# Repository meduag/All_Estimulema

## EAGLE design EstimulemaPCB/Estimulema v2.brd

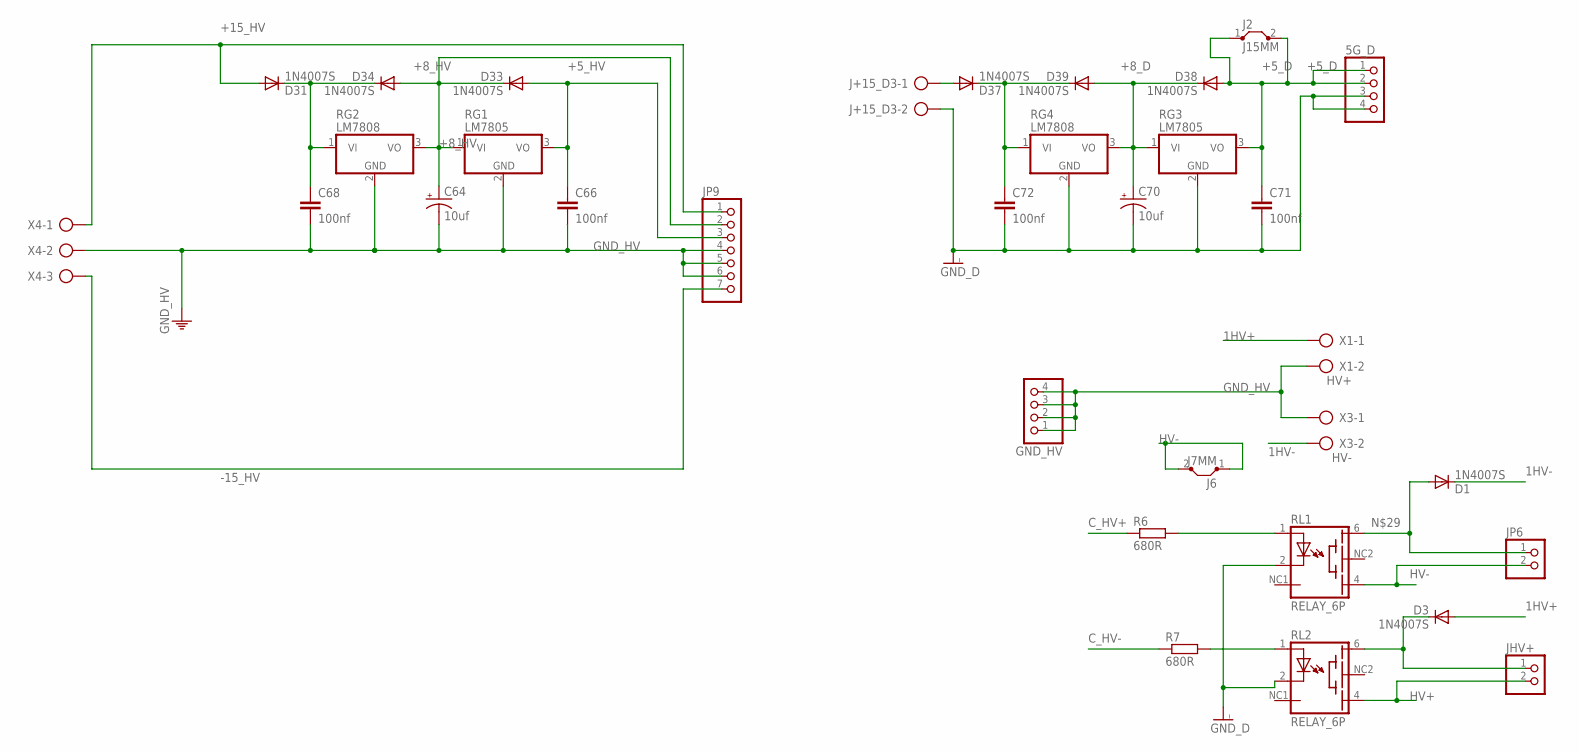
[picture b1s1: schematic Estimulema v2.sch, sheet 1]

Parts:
5G_D: PINHD-1X4; 1X04
C64, C70: 10uf; E2-5
C66, C68, C71, C72: 100nf; C025-024X044
D1, D3, D31, D33, D34, D37, D38, D39: 1N4007S; DIODO4MM
GND_HV: PINHD-1X4; 1X04
J2: J15MM; 15
J6: J7MM; 07
J+15_D3: AK300/2
JHV+: PINHD-1X2; 1X02
JP6: PINHD-1X2; 1X02
JP9: PINHD-1X7; 1X07
R6, R7: 680R; RESISTENCIA_0805
RG1, RG3: LM7805; TO220V
RG2, RG4: LM7808; TO220V
RL1, RL2: RELAY_6P; TS210
X1: HV+; AK300/2
X3: HV-; AK300/2
X4: AK300/3

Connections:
1HV+: D3.A, X1.1
1HV-: D1.C, X3.2
+5_D: 5G_D.1, 5G_D.2, C71.1, D38.A, J2.1, J2.2, RG3.3 (VO); also elsewhere on the board
+5_HV: C66.1, D33.A, JP9.3, RG1.3 (VO); also elsewhere on the board
+8_D: C70.+, D38.C, D39.A, RG3.1 (VI), RG4.3 (VO)
+8_HV: C64.+, D33.C, D34.A, JP9.2, RG1.1 (VI), RG2.3 (VO)
+15_HV: D31.A, JP9.1, X4.1; also elsewhere on the board
-15_HV: JP9.7, X4.3; also elsewhere on the board
C_HV+: R6.1; also elsewhere on the board
C_HV-: R7.1; also elsewhere on the board
GND_D: 5G_D.3, 5G_D.4, C70.-, C71.2, C72.2, J+15_D3.2, RG3.2 (GND), RG4.2 (GND), RL1.2 (C), RL2.2 (C); also elsewhere on the board
GND_HV: C64.-, C66.2, C68.2, GND_HV.1, GND_HV.2, GND_HV.3, GND_HV.4, JP9.4, JP9.5, JP9.6, RG1.2 (GND), RG2.2 (GND), X1.2, X3.1, X4.2; also elsewhere on the board
HV+: JHV+.2, RL2.4 (EMI); also elsewhere on the board
HV-: J6.1, J6.2, JP6.2, RL1.4 (EMI); also elsewhere on the board
unnamed: D37.A, J+15_D3.1
unnamed: R6.2, RL1.1 (A)
unnamed: R7.2, RL2.1 (A)
unnamed: D1.A, JP6.1, RL1.6 (BAS)
unnamed: D3.C, JHV+.1, RL2.6 (BAS)
unnamed: C68.1, D31.C, D34.C, RG2.1 (VI)
unnamed: C72.1, D37.C, D39.C, RG4.1 (VI)

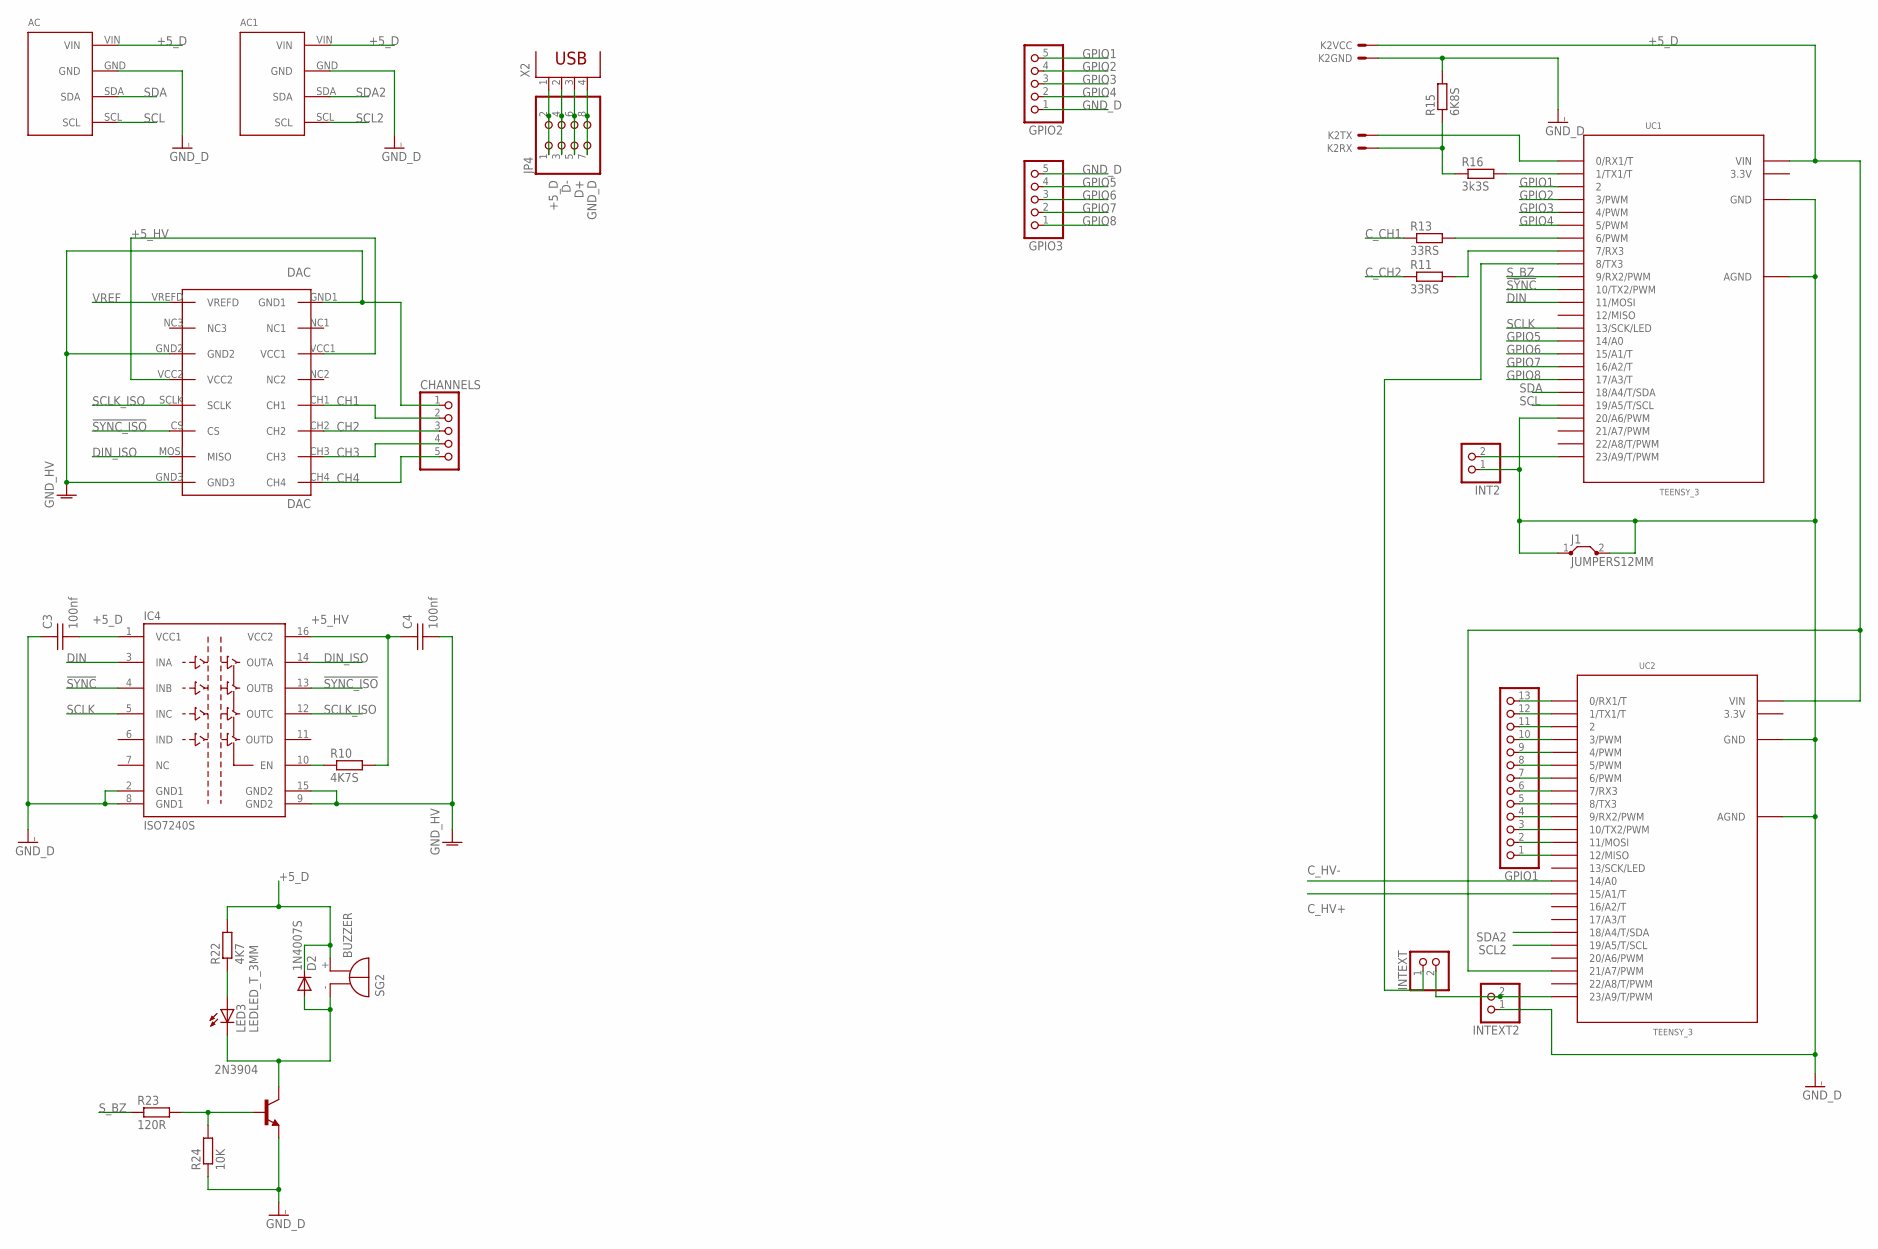
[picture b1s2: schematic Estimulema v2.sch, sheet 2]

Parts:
2N3904: 29-NPN-TO92-EBC; TO92-EBC
AC: CONECTOR_ACELEROMETRO_MPU6050CONECTOR_MPU6050; MPU6050
AC1: MPU6050
C3, C4: 100nf; CAP_CER_SMD-0805
CHANNELS: PINHD-1X5; 1X05
D2: 1N4007S; DIODO4MM
DAC: DAC; DACMOD_P
GPIO1: PINHD-1X13; 1X13
GPIO2, GPIO3: PINHD-1X5; 1X05
IC4: ISO7240S; SO-16DW
INT2: PINHD-1X2; 1X02
INTEXT, INTEXT2: PINHD-1X2; 1X02
J1: JUMPERS12MM; 12
JP4: PINHD-2X4; 2X04
K2: HC-06; CONECTOR_BTHC-06
LED3: LEDLED_T_3MM; LED3MM
R10: 4K7S; RESISTENCIA_0805
R11, R13: 33RS; RESISTENCIA_0805
R15: 6K8S; RESISTENCIA_0805
R16: 3k3S; RESISTENCIA_0805
R22: 4K7; RESISTENCIA_0805
R23: 120R; RESISTENCIA_0805
R24: 10K; RESISTENCIA_0805
SG2: BUZZER
UC1, UC2: TEENSY_3; TEENSY_3.0-3.2_DIL
X2: PN61729

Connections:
3.3V: UC1.3.3V, UC2.3.3V
!SYNC: IC4.4 (INB), UC1.10 (10/TX2/PWM)
!SYNC_ISO: DAC.CS, IC4.13 (OUTB)
+5_D: AC.VIN, AC1.VIN, C3.2, D2.C, IC4.1 (VCC1), JP4.1, JP4.2, K2.1, R22.2, SG2.+ (-), UC1.VIN, UC2.21/A7 (21/A7/PWM), UC2.VIN, X2.1; also elsewhere on the board
+5_HV: C4.1, DAC.VCC1, DAC.VCC2, IC4.16 (VCC2), R10.2; also elsewhere on the board
CH1: CHANNELS.2, DAC.CH1; also elsewhere on the board
CH2: CHANNELS.3, DAC.CH2; also elsewhere on the board
CH3: CHANNELS.4, DAC.CH3
CH4: CHANNELS.5, DAC.CH4
C_15D: GPIO1.11, UC2.2
C_CH1: R13.1; also elsewhere on the board
C_CH2: R11.1; also elsewhere on the board
C_HV+: UC2.15/A1 (15/A1/T); also elsewhere on the board
C_HV-: UC2.14/A0; also elsewhere on the board
D+: JP4.5, JP4.6, X2.3
D-: JP4.3, JP4.4, X2.2
DIN: IC4.3 (INA), UC1.11 (11/MOSI)
DIN_ISO: DAC.MOSI (MISO), IC4.14 (OUTA)
GNDI: C3.1, IC4.2 (GND1), IC4.8 (GND1)
GND_D: 2N3904.E, AC.GND, AC1.GND, GPIO2.1, GPIO3.5, INT2.1, INTEXT2.1, J1.1, J1.2, JP4.7, JP4.8, K2.2, R15.2, R24.1, UC1.20/A6 (20/A6/PWM), UC1.AGND, UC1.GND, UC2.AGND, UC2.GND, X2.4; also elsewhere on the board
GND_HV: C4.2, CHANNELS.1, DAC.GND1, DAC.GND2, DAC.GND3, IC4.9 (GND2), IC4.15 (GND2); also elsewhere on the board
GPIO1: GPIO2.5, UC1.2
GPIO2: GPIO2.4, UC1.3 (3/PWM)
GPIO3: GPIO2.3, UC1.4 (4/PWM)
GPIO4: GPIO2.2, UC1.5 (5/PWM)
GPIO5: GPIO3.4, UC1.14/A0
GPIO6: GPIO3.3, UC1.15/A1 (15/A1/T)
GPIO7: GPIO3.2, UC1.16/A2 (16/A2/T)
GPIO8: GPIO3.1, UC1.17/A3 (17/A3/T)
unnamed: INTEXT.2, INTEXT2.2, UC2.23/A9 (23/A9/T/PWM)
unnamed: INTEXT.1, UC1.8 (8/TX3)
unnamed: GPIO1.13, UC2.0 (0/RX1/T)
unnamed: GPIO1.12, UC2.1 (1/TX1/T)
unnamed: GPIO1.10, UC2.3 (3/PWM)
unnamed: GPIO1.9, UC2.4 (4/PWM)
unnamed: GPIO1.8, UC2.5 (5/PWM)
unnamed: GPIO1.7, UC2.6 (6/PWM)
unnamed: GPIO1.6, UC2.7 (7/RX3)
unnamed: GPIO1.5, UC2.8 (8/TX3)
unnamed: GPIO1.4, UC2.9 (9/RX2/PWM)
unnamed: GPIO1.3, UC2.10 (10/TX2/PWM)
unnamed: GPIO1.2, UC2.11 (11/MOSI)
unnamed: GPIO1.1, UC2.12 (12/MISO)
unnamed: IC4.10 (EN), R10.1
unnamed: R13.2, UC1.6 (6/PWM)
unnamed: R11.2, UC1.7 (7/RX3)
unnamed: K2.4, R15.1, R16.1
unnamed: R16.2, UC1.1 (1/TX1/T)
unnamed: K2.3, UC1.0 (0/RX1/T)
unnamed: LED3.A, R22.1
unnamed: 2N3904.C, D2.A, LED3.K (C), SG2.- (+)
unnamed: 2N3904.B, R23.2, R24.2
unnamed: INT2.2, UC1.23/A9 (23/A9/T/PWM)
SCL: AC.SCL, UC1.19/A5 (19/A5/T/SCL)
SCL2: AC1.SCL, UC2.19/A5 (19/A5/T/SCL)
SCLK: IC4.5 (INC), UC1.13 (13/SCK/LED)
SCLK_ISO: DAC.SCLK, IC4.12 (OUTC)
SDA: AC.SDA, UC1.18/A4 (18/A4/T/SDA)
SDA2: AC1.SDA, UC2.18/A4 (18/A4/T/SDA)
S_BZ: R23.1, UC1.9 (9/RX2/PWM)
VREF: DAC.VREFD; also elsewhere on the board

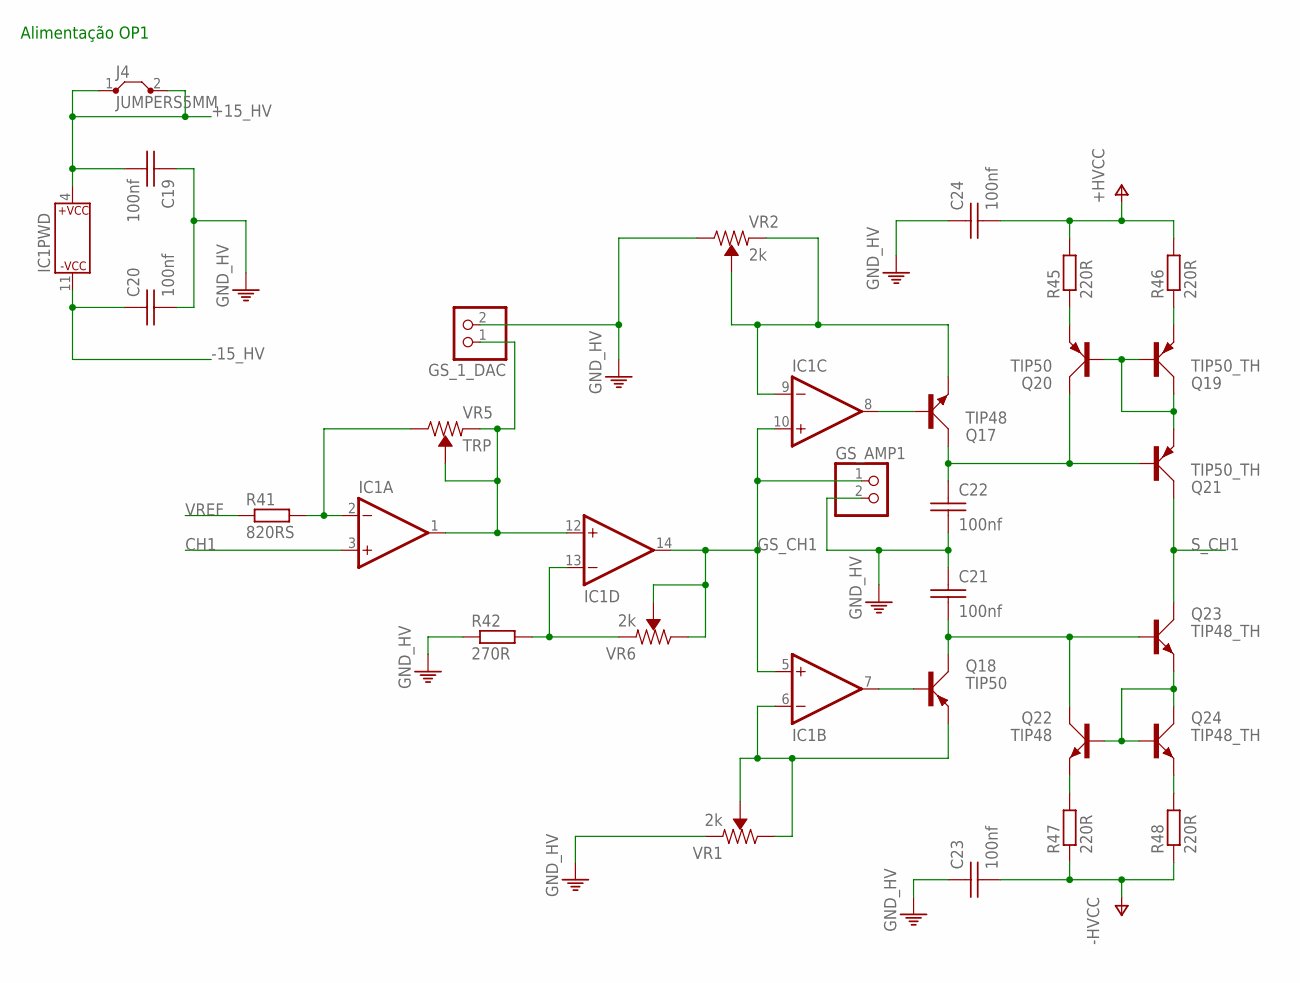
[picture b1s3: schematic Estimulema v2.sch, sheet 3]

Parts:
C19, C20: 100nf; CAP_CER_SMD-0805
C21, C22: 100nf; CAP_CER_2,54-5X5
C23, C24: 100nf; CAP_CER_16X7
GS_1_DAC: PINHD-1X2; 1X02
GS_AMP1: PINHD-1X2; 1X02
IC1: TL084; DIL14
J4: JUMPERS5MM; 05
Q17, Q22: TIP48; TO220
Q18, Q20: TIP50; TO220
Q19, Q21: TIP50_TH; TO220
Q23, Q24: TIP48_TH; TO220
R41: 820RS; RESISTENCIA_0805
R42: 270R; RESISTENCIA_0805
R45, R46, R47, R48: 220R; 0204V
VR1, VR2, VR6: 2k; TRIMPOT-PTH-3386U
VR5: TRP; TRIMPOT-PTH-3386U

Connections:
+15_HV: C19.2, IC1.4 (P$V+), J4.1, J4.2; also elsewhere on the board
-15_HV: C20.1, IC1.11 (P$V-); also elsewhere on the board
CH1: IC1.3 (+IN); also elsewhere on the board
GND_HV: C19.1, C20.2, C21.1, C22.2, C23.1, C24.1, GS_1_DAC.2, GS_AMP1.2, R42.1, VR1.1 (CCW), VR2.3 (CW); also elsewhere on the board
GS_CH1: GS_AMP1.1, IC1.5 (+IN), IC1.10 (+IN), IC1.14 (OUT), VR6.2 (WIPER), VR6.3 (CW)
HV+: C24.2, R45.2, R46.2; also elsewhere on the board
HV-: C23.2, R47.1, R48.1; also elsewhere on the board
unnamed: IC1.2 (-IN), R41.2, VR5.3 (CW)
unnamed: GS_1_DAC.1, IC1.1 (OUT), IC1.12 (+IN), VR5.1 (CCW), VR5.2 (WIPER)
unnamed: IC1.13 (-IN), R42.2, VR6.1 (CCW)
unnamed: IC1.9 (-IN), Q17.E, VR2.1 (CCW), VR2.2 (WIPER)
unnamed: IC1.6 (-IN), Q18.E, VR1.2 (WIPER), VR1.3 (CW)
unnamed: C21.2, Q18.C, Q22.C, Q23.B
unnamed: C22.1, Q17.C, Q20.C, Q21.B
unnamed: Q20.E, R45.1
unnamed: Q19.E, R46.1
unnamed: Q19.B, Q19.C, Q20.B, Q21.E
unnamed: Q22.B, Q23.E, Q24.B, Q24.C
unnamed: Q22.E, R47.2
unnamed: Q24.E, R48.2
unnamed: IC1.8 (OUT), Q17.B
unnamed: IC1.7 (OUT), Q18.B
S_CH1: Q21.C, Q23.C; also elsewhere on the board
VREF: R41.1; also elsewhere on the board

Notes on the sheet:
Alimentação OP1

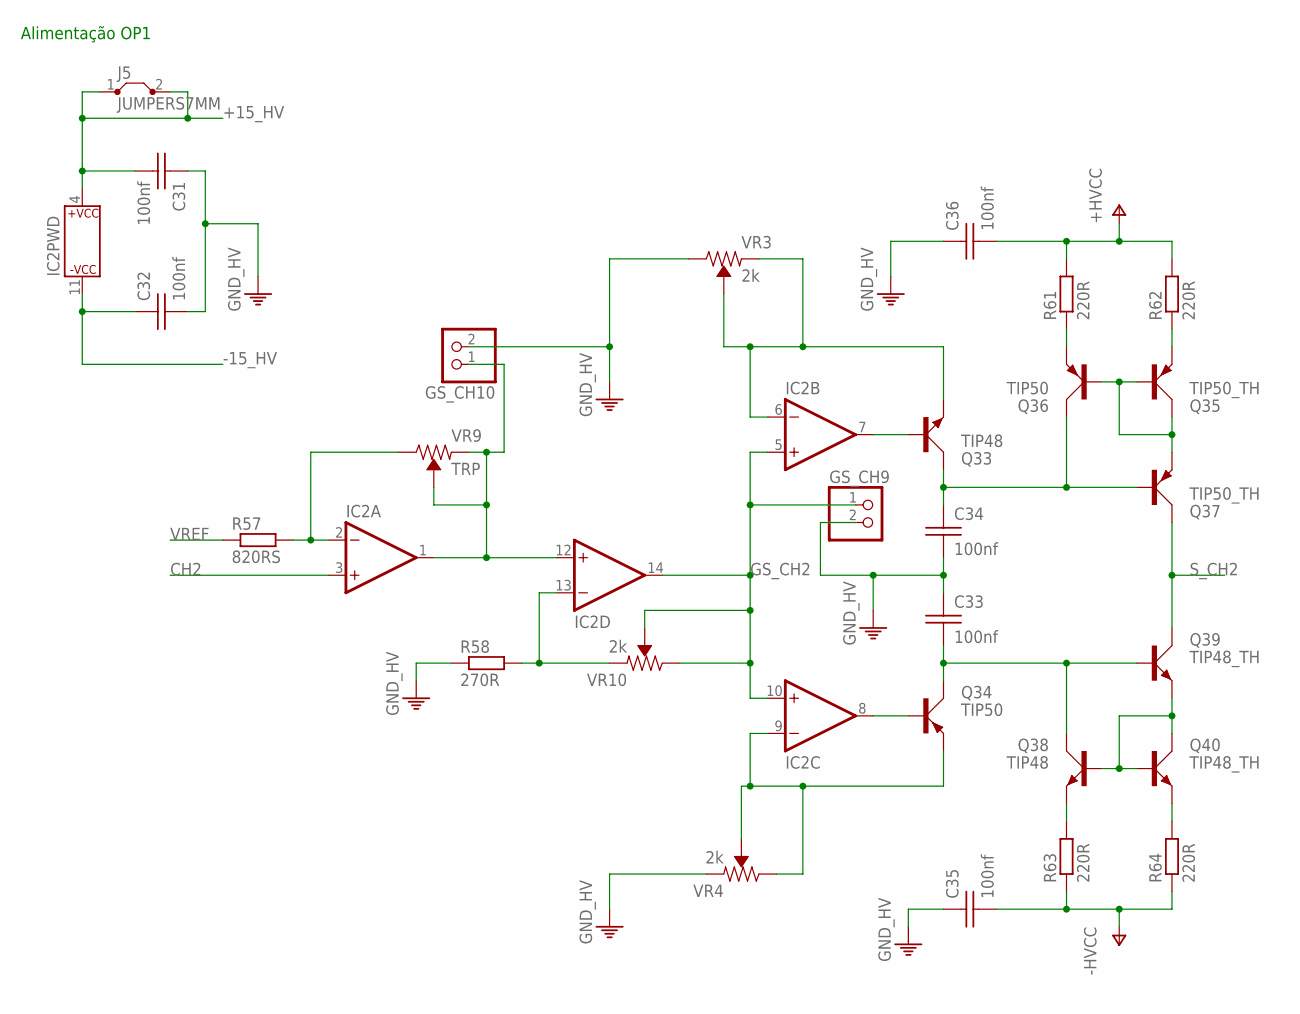
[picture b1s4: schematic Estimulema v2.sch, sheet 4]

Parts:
C31, C32: 100nf; CAP_CER_SMD-0805
C33, C34: 100nf; CAP_CER_2,54-5X5
C35, C36: 100nf; CAP_CER_16X7
GS_CH9, GS_CH10: PINHD-1X2; 1X02
IC2: TL084; DIL14
J5: JUMPERS7MM; 07
Q33, Q38: TIP48; TO220
Q34, Q36: TIP50; TO220
Q35, Q37: TIP50_TH; TO220
Q39, Q40: TIP48_TH; TO220
R57: 820RS; RESISTENCIA_0805
R58: 270R; RESISTENCIA_0805
R61, R62, R63, R64: 220R; 0204V
VR3, VR4, VR10: 2k; TRIMPOT-PTH-3386U
VR9: TRP; TRIMPOT-PTH-3386U

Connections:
+15_HV: C31.2, IC2.4 (P$V+), J5.1, J5.2; also elsewhere on the board
-15_HV: C32.1, IC2.11 (P$V-); also elsewhere on the board
CH2: IC2.3 (+IN); also elsewhere on the board
GND_HV: C31.1, C32.2, C33.1, C34.2, C35.1, C36.1, GS_CH9.2, GS_CH10.2, R58.1, VR3.3 (CW), VR4.1 (CCW); also elsewhere on the board
GS_CH2: GS_CH9.1, IC2.5 (+IN), IC2.10 (+IN), IC2.14 (OUT), VR10.2 (WIPER), VR10.3 (CW)
HV+: C36.2, R61.2, R62.2; also elsewhere on the board
HV-: C35.2, R63.1, R64.1; also elsewhere on the board
unnamed: IC2.2 (-IN), R57.2, VR9.3 (CW)
unnamed: GS_CH10.1, IC2.1 (OUT), IC2.12 (+IN), VR9.1 (CCW), VR9.2 (WIPER)
unnamed: IC2.13 (-IN), R58.2, VR10.1 (CCW)
unnamed: IC2.6 (-IN), Q33.E, VR3.1 (CCW), VR3.2 (WIPER)
unnamed: IC2.9 (-IN), Q34.E, VR4.2 (WIPER), VR4.3 (CW)
unnamed: C33.2, Q34.C, Q38.C, Q39.B
unnamed: C34.1, Q33.C, Q36.C, Q37.B
unnamed: Q36.E, R61.1
unnamed: Q35.E, R62.1
unnamed: Q35.B, Q35.C, Q36.B, Q37.E
unnamed: Q38.B, Q39.E, Q40.B, Q40.C
unnamed: Q38.E, R63.2
unnamed: Q40.E, R64.2
unnamed: IC2.7 (OUT), Q33.B
unnamed: IC2.8 (OUT), Q34.B
S_CH2: Q37.C, Q39.C; also elsewhere on the board
VREF: R57.1; also elsewhere on the board

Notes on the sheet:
Alimentação OP1

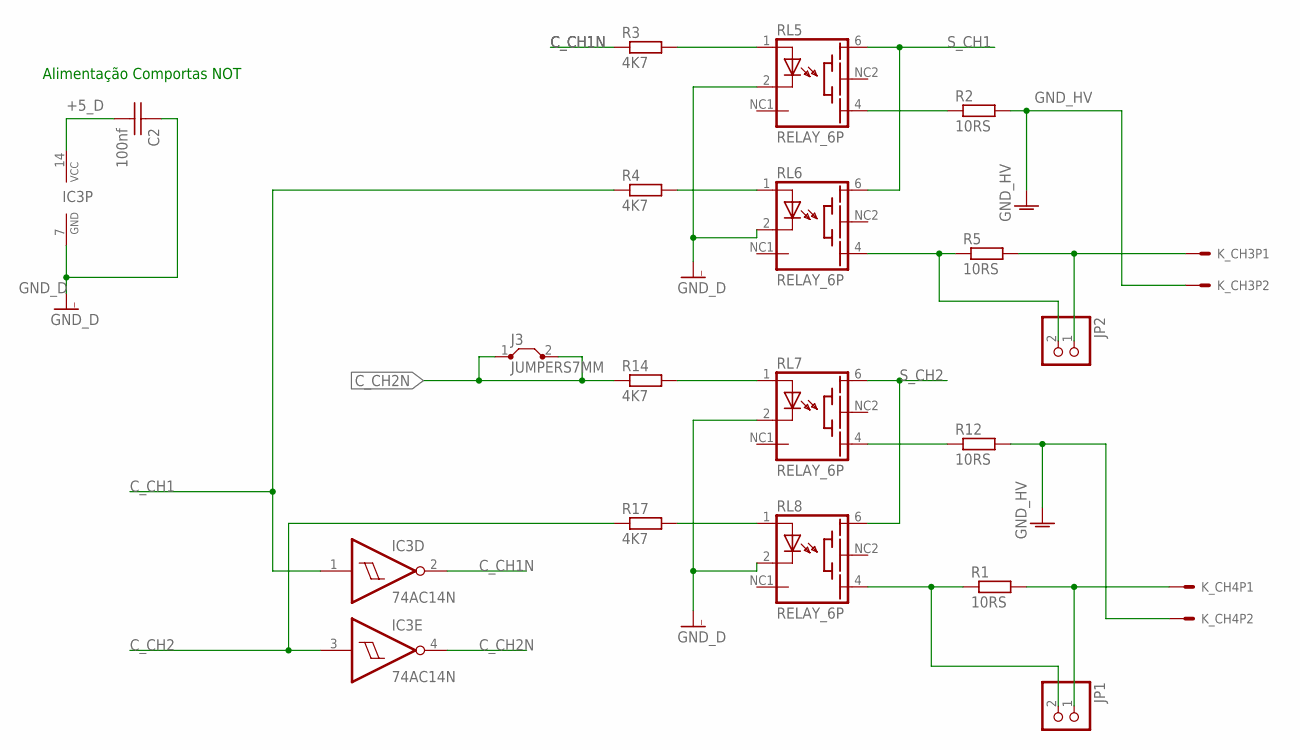
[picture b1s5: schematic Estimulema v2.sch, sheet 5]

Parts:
C2: 100nf; CAP_CER_SMD-0805
IC3: 74AC14N; DIL14
J3: JUMPERS7MM; 07
JP1, JP2: PINHD-1X2; 1X02
K_CH3, K_CH4: CONECTOR_5.08; CONECTOR_X2_5.08
R1, R5: 10RS; 0204/5
R2, R12: 10RS; 0617V
R3, R4, R14, R17: 4K7; RESISTENCIA_0805
RL5, RL6, RL7, RL8: RELAY_6P; TS210

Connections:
+5_D: C2.2, IC3.14 (VCC); also elsewhere on the board
C_CH1: IC3.1 (I), R4.1; also elsewhere on the board
C_CH1N: IC3.2 (O), R3.1
C_CH2: IC3.3 (I), R17.1; also elsewhere on the board
C_CH2N: IC3.4 (O), J3.1, J3.2, R14.1
GND_D: C2.1, IC3.7 (GND), RL5.2 (C), RL6.2 (C), RL7.2 (C), RL8.2 (C); also elsewhere on the board
GND_HV: K_CH3.2, K_CH4.2, R2.2, R12.2; also elsewhere on the board
unnamed: R3.2, RL5.1 (A)
unnamed: R4.2, RL6.1 (A)
unnamed: R2.1, RL5.4 (EMI)
unnamed: JP2.2, R5.1, RL6.4 (EMI)
unnamed: R14.2, RL7.1 (A)
unnamed: R17.2, RL8.1 (A)
unnamed: R12.1, RL7.4 (EMI)
unnamed: JP2.1, K_CH3.1, R5.2
unnamed: JP1.1, K_CH4.1, R1.2
unnamed: JP1.2, R1.1, RL8.4 (EMI)
S_CH1: RL5.6 (BAS), RL6.6 (BAS); also elsewhere on the board
S_CH2: RL7.6 (BAS), RL8.6 (BAS); also elsewhere on the board

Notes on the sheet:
Alimentação Comportas NOT

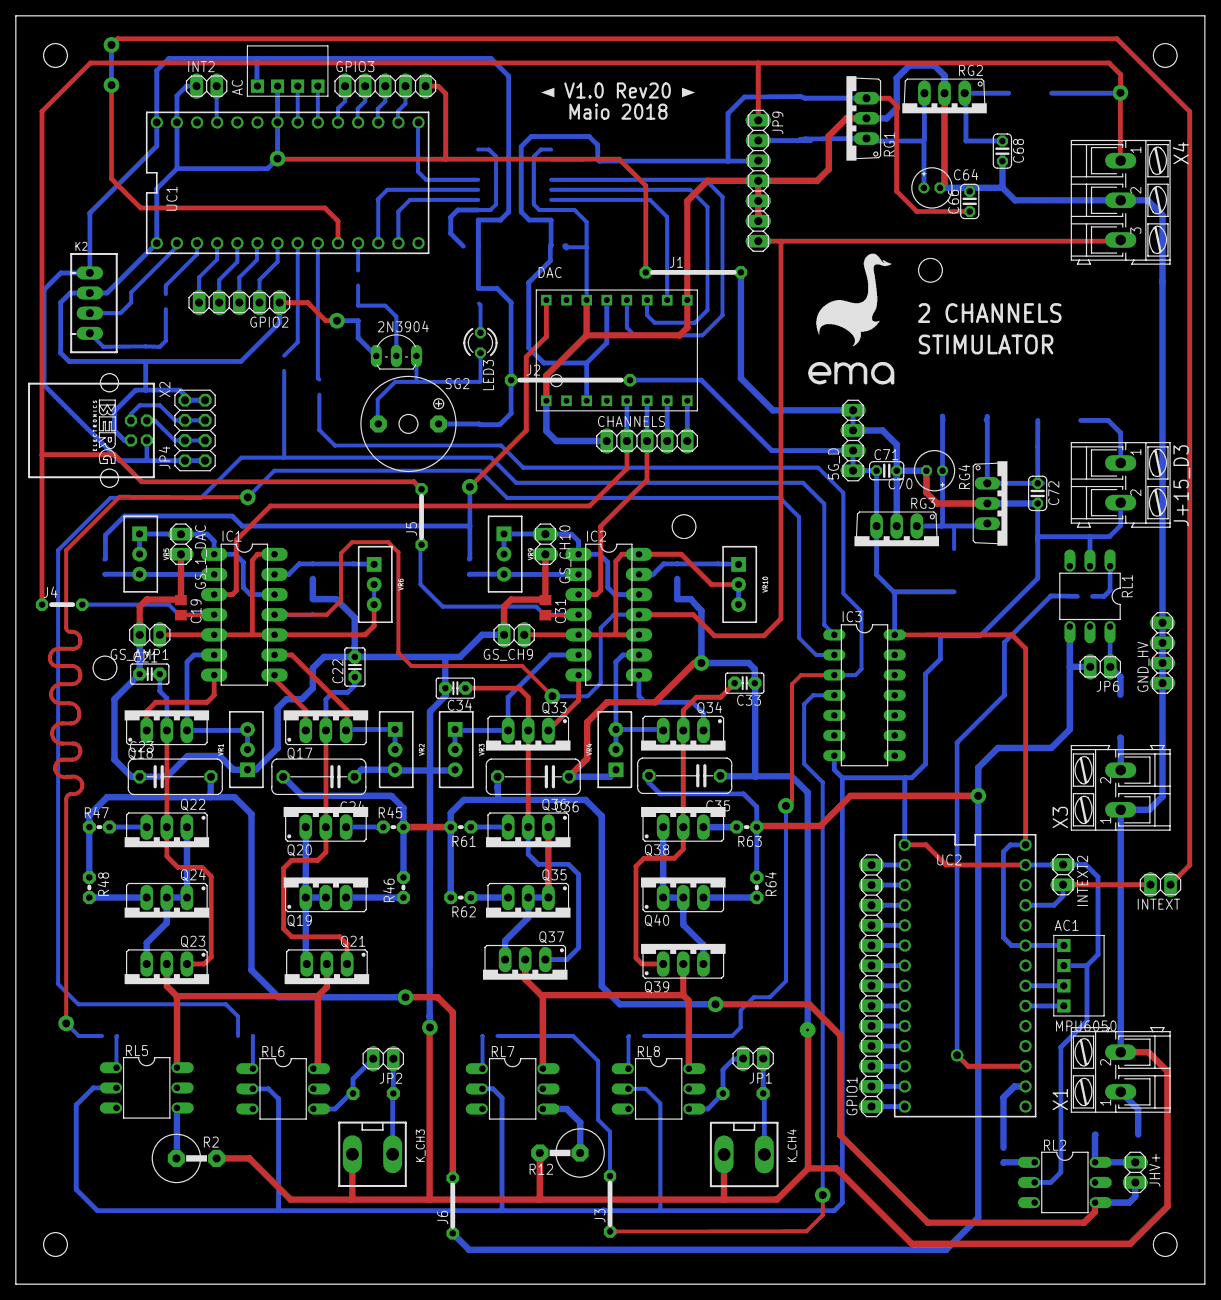
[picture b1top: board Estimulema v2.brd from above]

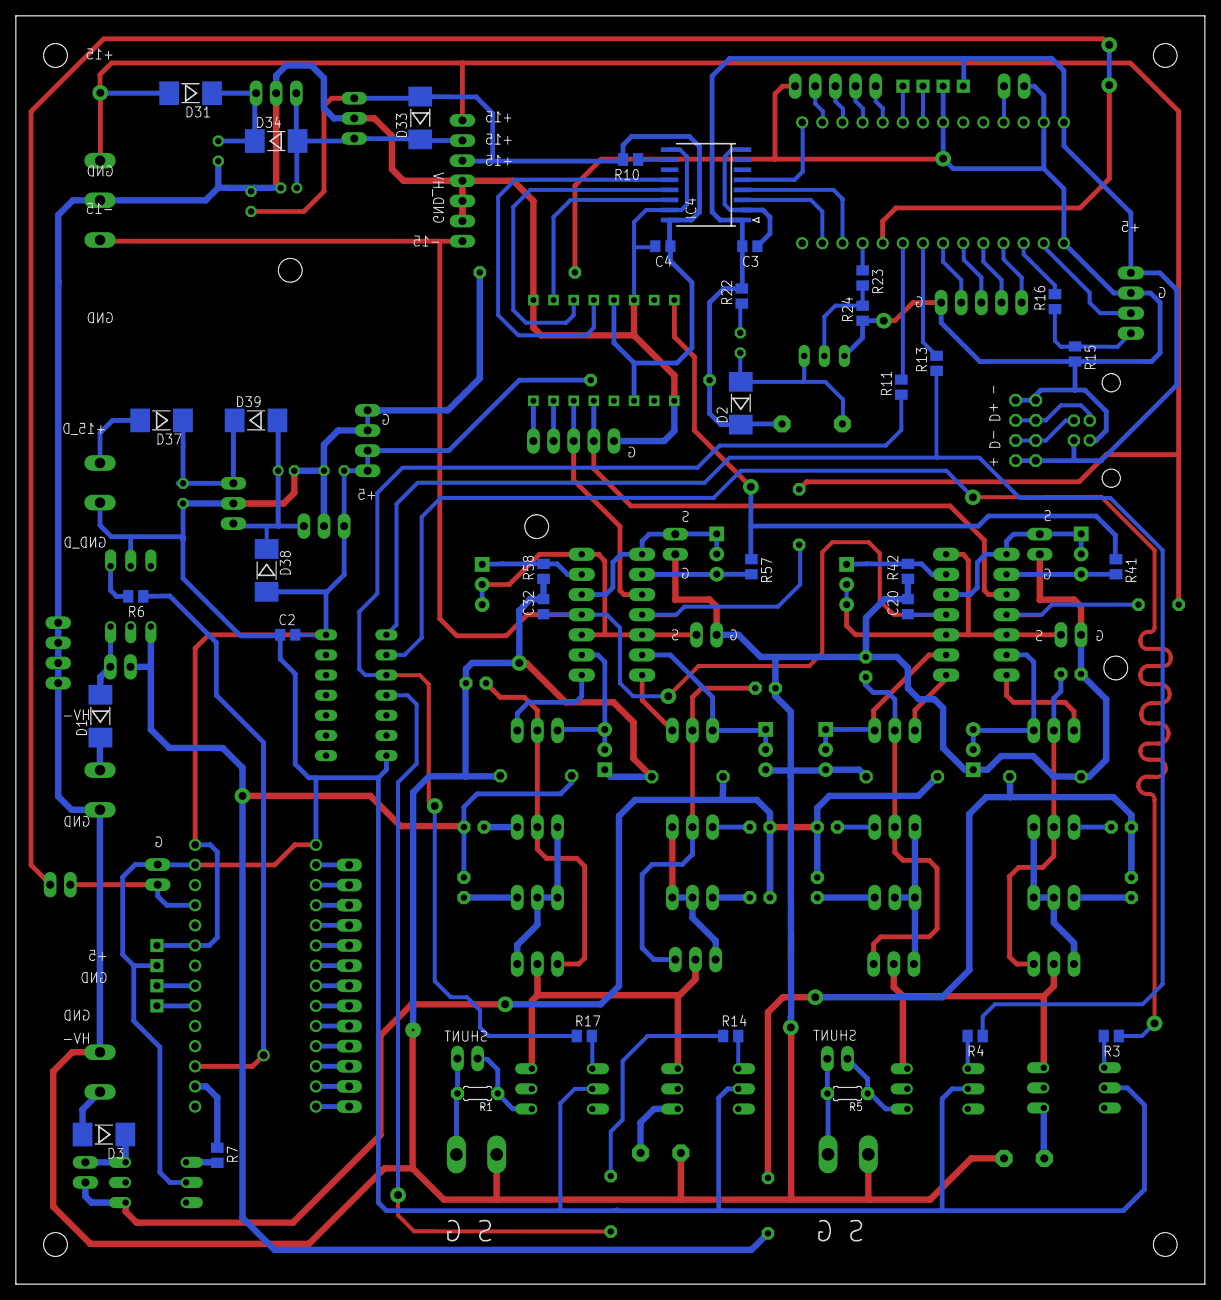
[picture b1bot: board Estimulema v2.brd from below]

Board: 2 copper layers, 150.0 x 160.0 mm, 139 parts (35 on the bottom side), 122 nets.

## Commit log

2018-05-09 Todos los archivos
    actualizndo version inicial del estimulema
